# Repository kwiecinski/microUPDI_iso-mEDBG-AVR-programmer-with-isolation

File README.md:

# microUPDI\_iso

DIY UPDI programmer with additional data line isolators, allowing you to safely work on high-voltage (HV) projects.

This project is based on the original [microUPDI project by MCUdude](https://github.com/MCUdude/microUPDI),\
and the firmware is sourced from [microUPDIcore](https://github.com/MCUdude/microUPDIcore).

<div style="display: flex; justify-content: space-around; align-items: center;">

</div>

---

### IMPORTANT

You might find references stating that the mEDBG programmer supports the AVR-Dx series of microcontrollers:\
[Microchip Device Support Documentation](https://packs.download.microchip.com/DeviceDoc/Device_Support.pdf).

However, **this is not true!** The microUPDI programmer does not support the AVR-Dx series. It is compatible only with the megaAVR-0 and tinyAVR-0/1/2 series. All device and firmware updates are available from the Microchip Packs website, but the mEDBG has not seen significant updates in years.

---

### Hardware

The microUPDI programmer is built on the **Pro Micro 5V/16MHz** board, which uses the ATmega32U4 microcontroller. I purchased it cheaply from China, and it works just fine.

To isolate the data and power lines, you need the following components:

- **ADuM1250**: A bidirectional digital data isolator for the UPDI interface.
- **ADuM1281**: A dual-channel isolator for UART RX and TX lines.

For UART, any isolator capable of handling these lines will suffice; it doesn’t have to be the ADuM1281 specifically. However, for UPDI, the isolator must support bidirectional communication. I tested the ADuM1250 (designed for I²C), and it works correctly in this context.

---

### Software

#### Flashing the Firmware

The original method suggested by MCUdude involves using the Arduino IDE to upload `.hex` and `.eep` files to the Pro Micro board using the bootloader. Unfortunately, I encountered compilation issues with this approach.

Instead, I used **avrdude** to program the board. Ensure you are using the latest version of avrdude.

---

#### Checking the Bootloader

Before proceeding, identify the bootloader type on your Pro Micro board.\
To program the board using the bootloader, you need to reset the Pro Micro. After resetting, a new COM port will appear:

- For example, the board might normally use `COM11`, but after a reset, you’ll see `COM12` for the bootloader.

To extend the bootloader activation time, use the **double-reset** method. Quickly reset the board twice, and you’ll have 8 seconds (instead of the default 3 seconds) to upload the firmware.\
[Learn more about the Pro Micro bootloader here](https://learn.sparkfun.com/tutorials/pro-micro--fio-v3-hookup-guide/troubleshooting-and-faq).

---

#### Using avrdude

Run the following command to verify communication with the board:

```bash
avrdude.exe -C avrdude.conf -c avr109 -P COM12 -patmega32u4 -v
```

Explanation of the parameters:

- `-v`: Enables verbose mode for detailed output.
- `-c avr109`: Specifies the bootloader protocol (Caterina in this case).
- `-P COM12`: Selects the bootloader COM port.

If communication is successful, you’ll see details about the device signature and bootloader. If you encounter a “not in sync” error, your bootloader might differ or require alternative settings.

For me, the bootloader type was `avr109`.

For more options, consult the [avrdude documentation](https://avrdudes.github.io/avrdude/7.3/avrdude_4.html).

---

#### Using the Load\_firmware.bat Script

You can use a slightly modified version of MCUdude’s script to load the firmware.

Update the script with the paths to `avrdude.exe` and `avrdude.conf`:

```bat
SET AVRDUDE_PATH=avrdude.exe
SET AVRDUDE_CONF_PATH=avrdude.conf
```

Set the programmer type based on your bootloader:

```bat
SET PROGRAMMER=avr109
```

Specify the COM port that appears after resetting the board:

```bat
SET EXTRA_FLAGS=-P COM12 -b57600
```

Target-specific settings:

```bat
SET TARGET=atmega32u4
SET FLASH_FILE=mEDBG_UPDI.hex
SET EEPROM_FILE=mEDBG_UPDI.eep
```

Make sure all files are in the same directory as the `Load_firmware.bat` script.

---

#### Example Output

If everything is configured correctly, you should see output like this:

```plaintext
Programmer Type : butterfly
Description     : Atmel AppNote AVR109 Boot Loader

Connecting to programmer: .
Found programmer: Id = "CATERIN"; type = S
    Software Version = 1.0; No Hardware Version given.
Programmer supports auto addr increment.
Programmer supports buffered memory access with buffersize=128 bytes.

Programmer supports the following devices:
    Device code: 0x44

avrdude.exe: devcode selected: 0x44
avrdude.exe: AVR device initialized and ready to accept instructions

Reading | ################################################## | 100% 0.00s

avrdude.exe: Device signature = 0x1e9587 (probably m32u4)
avrdude.exe: safemode: hfuse reads as D8
avrdude.exe: safemode: efuse reads as CB

avrdude.exe: safemode: Fuses OK (E:CB, H:D8, L:FF)

avrdude.exe done.  Thank you.
```

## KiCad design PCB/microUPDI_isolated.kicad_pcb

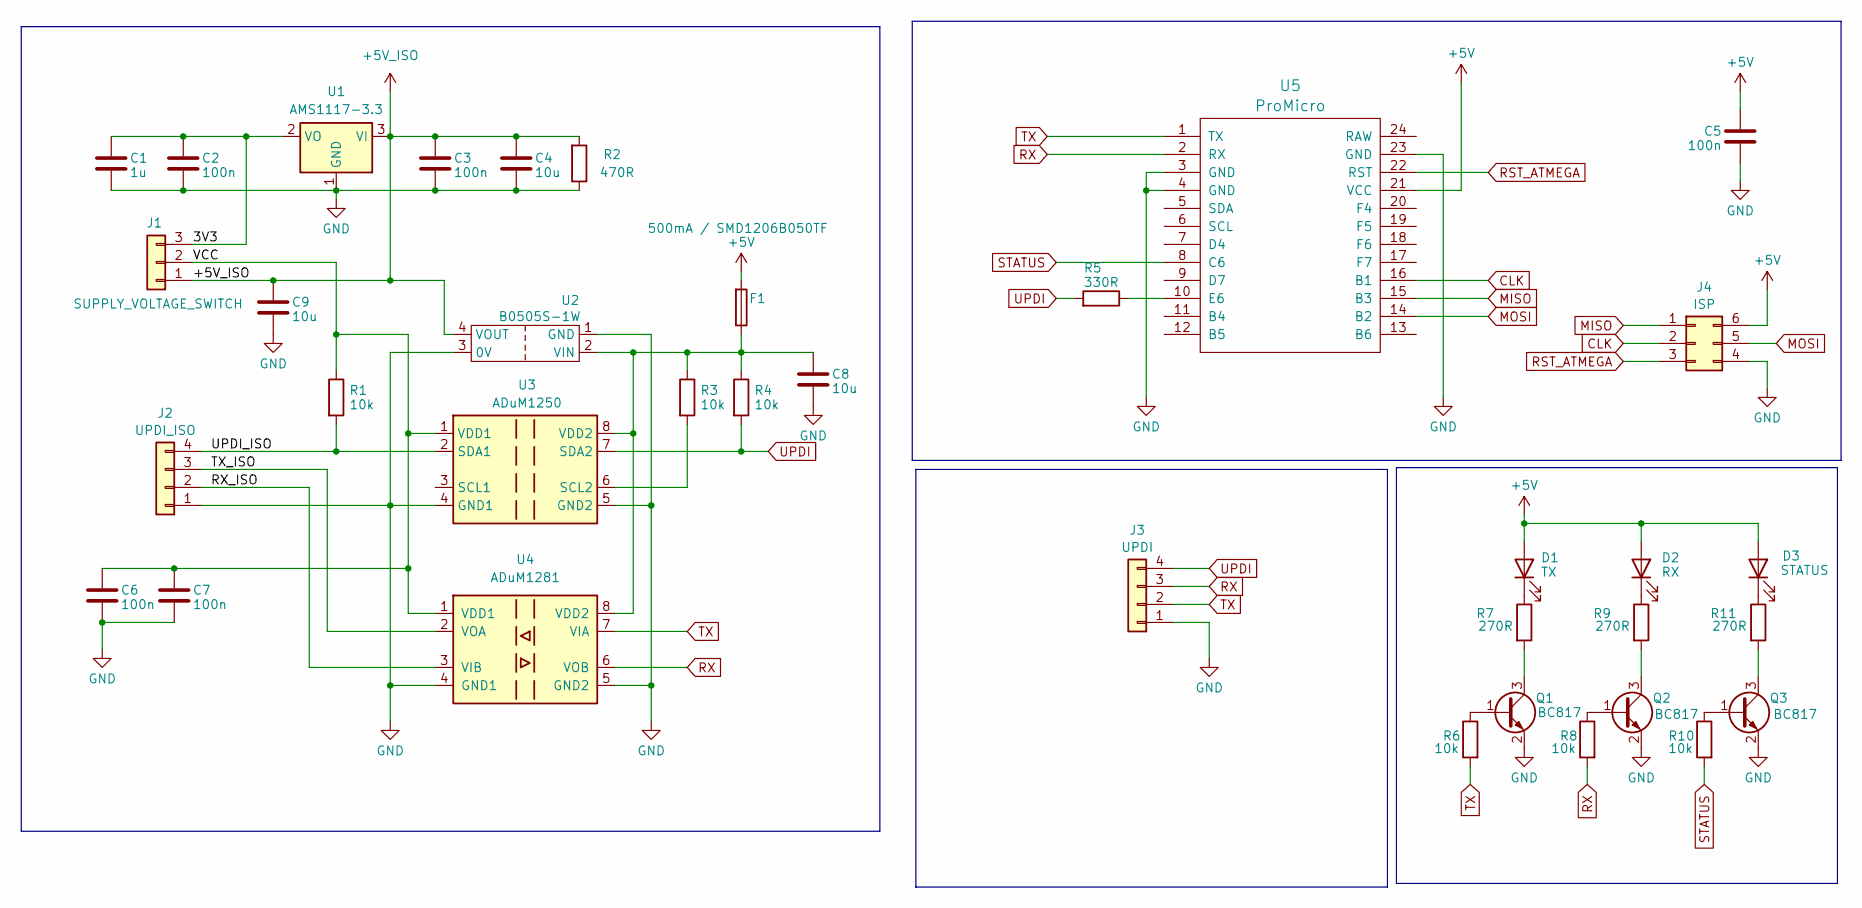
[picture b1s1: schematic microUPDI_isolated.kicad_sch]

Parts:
C1: 1u; C_0805_2012Metric
C2, C3, C5, C6, C7: 100n; C_0805_2012Metric
C4: 10u; C_0805_2012Metric
C8, C9: 10u; CP_EIA-3528-21_Kemet-B
D1: TX; LED_PLCC-2_3.4x3.0mm_AK
D2: RX; LED_PLCC-2_3.4x3.0mm_AK
D3: STATUS; LED_PLCC-2_3.4x3.0mm_AK
F1: 500mA / SMD1206B050TF; Fuse_1206_3216Metric
J1: SUPPLY_VOLTAGE_SWITCH; PinHeader_1x03_P2.54mm_Vertical
J2: UPDI_ISO; PinHeader_1x04_P2.54mm_Vertical_littleBigger
J3: UPDI; PinHeader_1x04_P2.54mm_Vertical_littleBigger
J4: ISP; PinHeader_2x03_P2.54mm_Vertical
Q1, Q2, Q3: BC817; SOT-23
R1, R3, R4, R6, R8, R10: 10k; R_0805_2012Metric
R2: 470R; R_0805_2012Metric
R5: 330R; R_0805_2012Metric
R7, R9, R11: 270R; R_0805_2012Metric
U1: AMS1117-3.3; SOT-223-3_TabPin2
U2: B0505S-1W; B0505S
U3: ADuM1250; SOIC-8_3.9x4.9mm_P1.27mm
U4: ADuM1281; SOIC-8_3.9x4.9mm_P1.27mm
U5: ProMicro

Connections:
+5V: C5.1, D1.2 (A), D2.2 (A), D3.2 (A), F1.2, J4.6, U5.21 (VCC)
+5V_ISO: C3.1, C4.1, C9.1, J1.1, R2.2, U1.3 (VI), U2.4 (VOUT)
/3V3: C1.1, C2.1, J1.3, U1.2 (VO)
/RX_ISO: J2.2, U4.3 (VIB)
/TX_ISO: J2.3, U4.2 (VOA)
/UPDI_ISO: J2.4, R1.2, U3.2 (SDA1)
/VCC: C6.1, C7.1, J1.2, R1.1, U3.1 (VDD1), U4.1 (VDD1)
CLK: J4.2, U5.16 (B1)
GND: C1.2, C2.2, C3.2, C4.2, C5.2, C6.2, C7.2, C8.2, C9.2, J2.1, J3.1, J4.4, Q1.2 (E), Q2.2 (E), Q3.2 (E), R2.1, U1.1 (GND), U2.1 (GND), U2.3 (0V), U3.4 (GND1), U3.5 (GND2), U4.4 (GND1), U4.5 (GND2), U5.3 (GND), U5.4 (GND), U5.23 (GND)
MISO: J4.1, U5.15 (B3)
MOSI: J4.5, U5.14 (B2)
unnamed: D1.1 (K), R7.1
unnamed: D2.1 (K), R9.1
unnamed: D3.1 (K), R11.1
unnamed: Q1.1 (B), R6.1
unnamed: Q1.3 (C), R7.2
unnamed: Q2.1 (B), R8.1
unnamed: Q2.3 (C), R9.2
unnamed: Q3.1 (B), R10.1
unnamed: Q3.3 (C), R11.2
unnamed: C8.1, F1.1, R3.1, R4.1, U2.2 (VIN), U3.8 (VDD2), U4.8 (VDD2)
unnamed: R3.2, U3.6 (SCL2)
unnamed: R5.1, U5.10 (E6)
RST_ATMEGA: J4.3, U5.22 (RST)
RX: J3.3, R8.2, U4.6 (VOB), U5.2 (RX)
STATUS: R10.2, U5.8 (C6)
TX: J3.2, R6.2, U4.7 (VIA), U5.1 (TX)
UPDI: J3.4, R4.2, R5.2, U3.7 (SDA2)

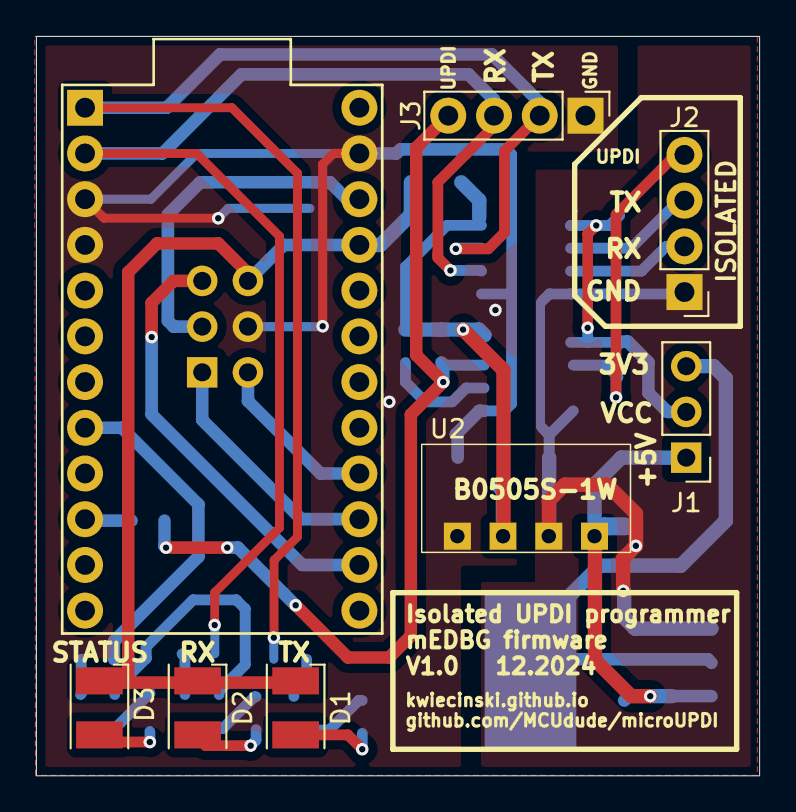
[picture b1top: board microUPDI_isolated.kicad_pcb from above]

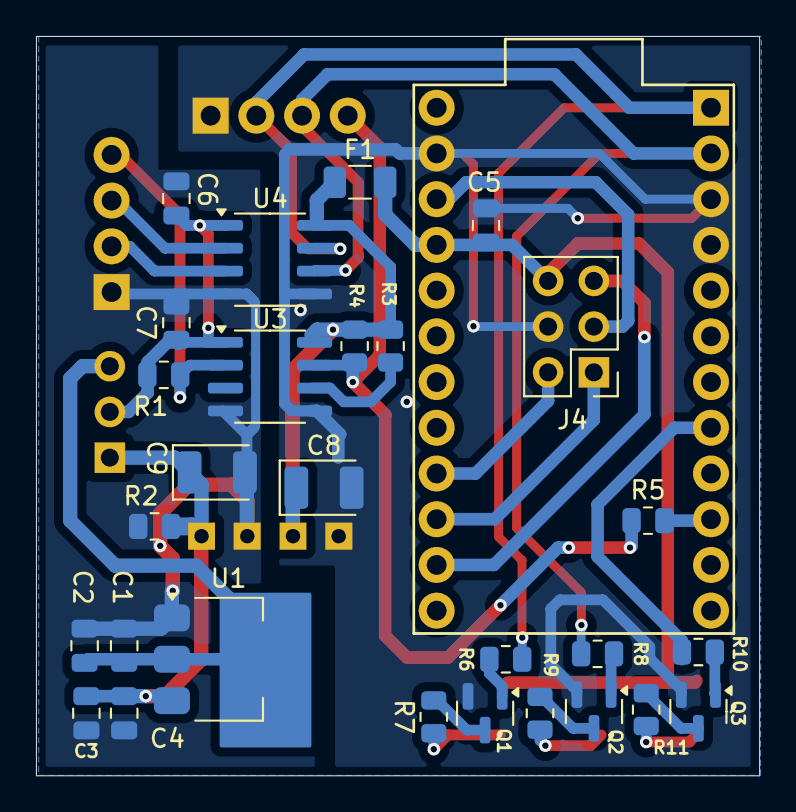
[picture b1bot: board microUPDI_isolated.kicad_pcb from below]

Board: 2 copper layers, 40.2 x 41.1 mm, 36 parts (28 on the bottom side), 28 nets.

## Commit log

2025-01-09 Update readme and PCB
